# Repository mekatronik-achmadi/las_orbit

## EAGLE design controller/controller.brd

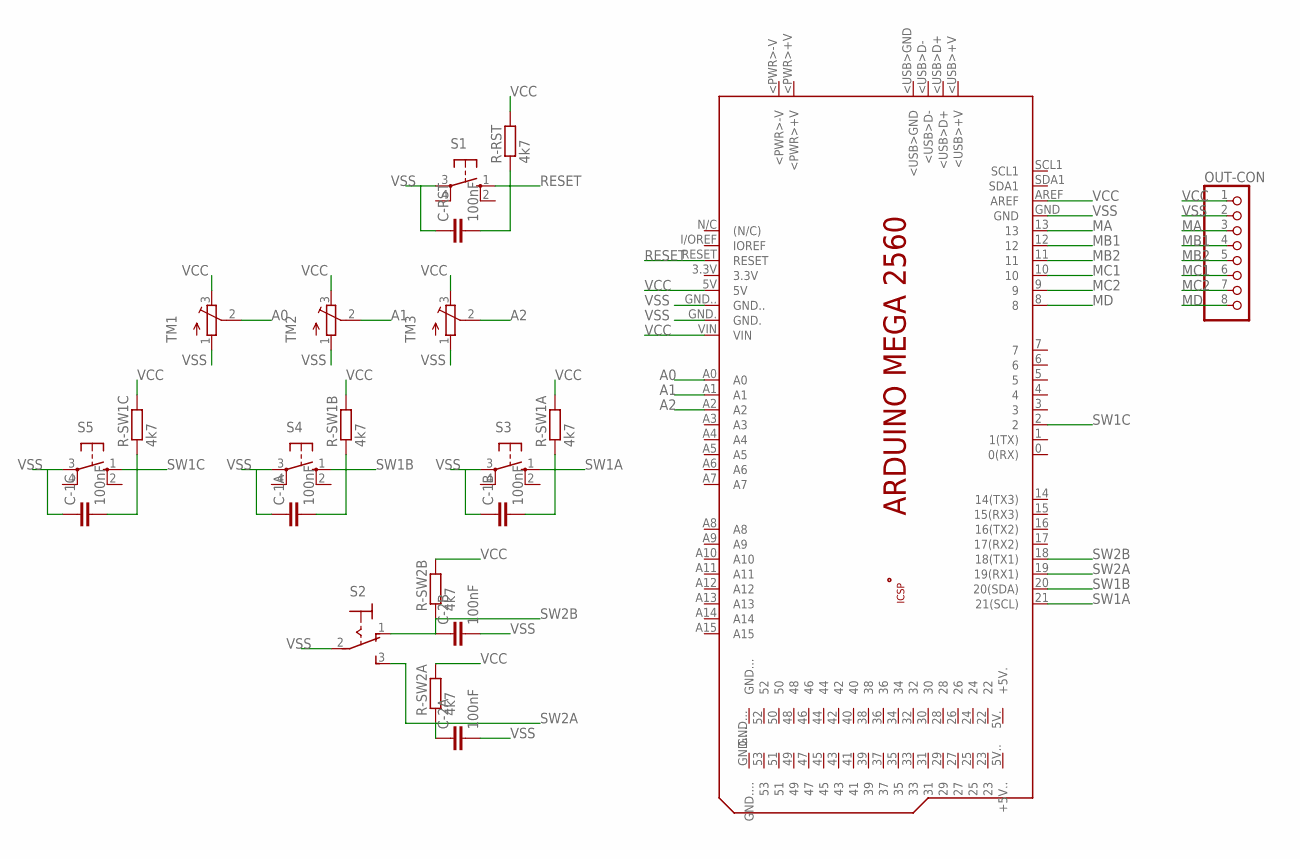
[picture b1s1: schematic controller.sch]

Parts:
C-1A, C-1B, C-1C, C-2A, C-2B: 100nF; C025-024X044
C-RST: 100nF; C025-024X044
OUT-CON: PINHD-1X8; 1X08
PCB1: ARDUINO_MEGA2560
R-RST: 4k7; 0204/7
R-SW1A, R-SW1B, R-SW1C, R-SW2A, R-SW2B: 4k7; 0204/7
S1, S3, S4, S5: 10-XX; B3F-10XX
S2: M9040P
TM1, TM2, TM3: TRIMPOT3386; TRIM-3386

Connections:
A0: PCB1.A0, TM1.2 (S)
A1: PCB1.A1, TM2.2 (S)
A2: PCB1.A2, TM3.2 (S)
MA: OUT-CON.3, PCB1.13
MB1: OUT-CON.4, PCB1.12
MB2: OUT-CON.5, PCB1.11
MC1: OUT-CON.6, PCB1.10
MC2: OUT-CON.7, PCB1.9
MD: OUT-CON.8, PCB1.8
RESET: C-RST.2, PCB1.RESET, R-RST.1, S1.1 (S)
SW1A: C-1B.2, PCB1.21 (21(SCL)), R-SW1A.1, S3.1 (S)
SW1B: C-1A.2, PCB1.20 (20(SDA)), R-SW1B.1, S4.1 (S)
SW1C: C-1C.2, PCB1.2, R-SW1C.1, S5.1 (S)
SW2A: C-2A.1, PCB1.19 (19(RX1)), R-SW2A.1, S2.3 (S)
SW2B: C-2B.1, PCB1.18 (18(TX1)), R-SW2B.1, S2.1 (O)
VCC: OUT-CON.1, PCB1.5V, PCB1.AREF, PCB1.VIN, R-RST.2, R-SW1A.2, R-SW1B.2, R-SW1C.2, R-SW2A.2, R-SW2B.2, TM1.3 (E), TM2.3 (E), TM3.3 (E)
VSS: C-1A.1, C-1B.1, C-1C.1, C-2A.2, C-2B.2, C-RST.1, OUT-CON.2, PCB1.GND, PCB1.GND., PCB1.GND.., S1.3, S2.2, S3.3, S4.3, S5.3, TM1.1 (A), TM2.1 (A), TM3.1 (A)

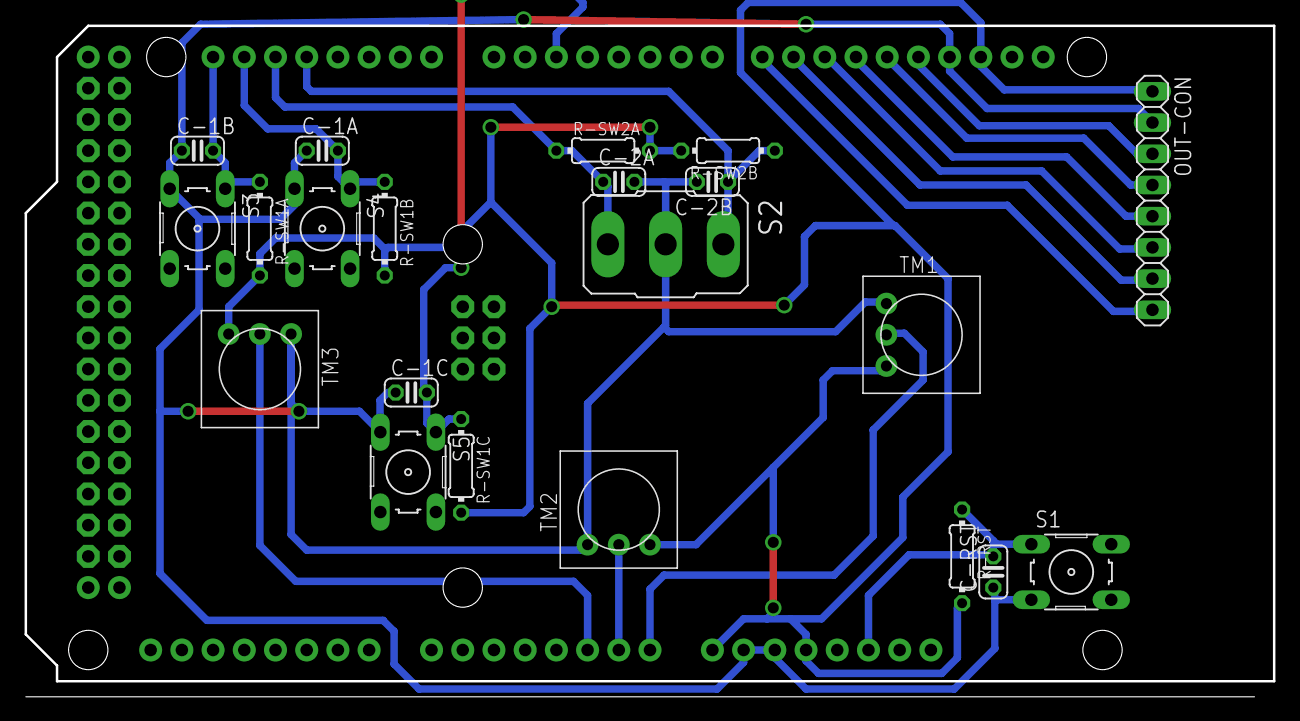
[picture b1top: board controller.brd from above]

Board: 2 copper layers, 101.6 x 54.6 mm, 22 parts (1 on the bottom side), 17 nets.

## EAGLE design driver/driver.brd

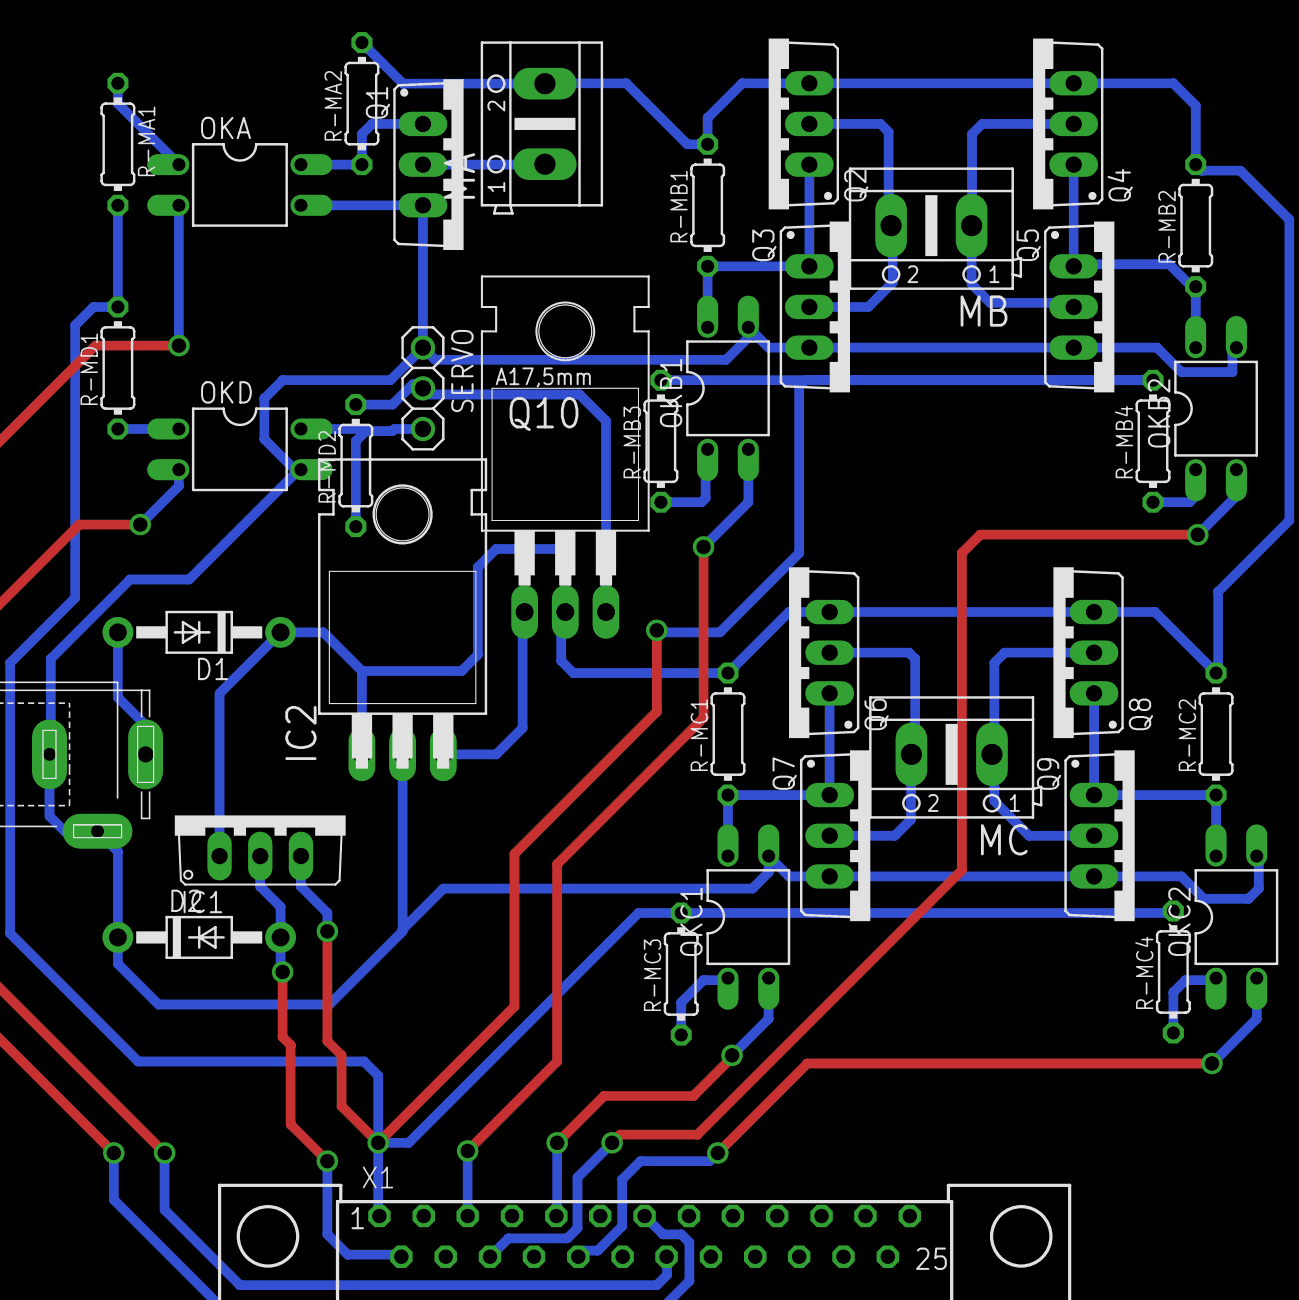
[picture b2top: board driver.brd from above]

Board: 2 copper layers, 38 parts (0 on the bottom side), 30 nets.

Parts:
D1, D2: 1N4004; DO41-10
IC1: 7805TV; TO220V
IC2: 7806T; TO220H
J1: SPC4077
MA: AK500/2
MB: AK500/2
MC: AK500/2
OKA: PC817; DIL04
OKB1, OKB2: PC817; DIL04
OKC1, OKC2: PC817; DIL04
OKD: PC817; DIL04
Q1, Q3, Q5, Q7, Q9: IRF530; TO220BV
Q2, Q4, Q6, Q8: IRF9530; TO220BV
Q10: TIP31C; TO220
R-MA1: 330; 0204/7
R-MA2: 4k7; 0204/7
R-MB1, R-MB2: 4k7; 0204/7
R-MB3, R-MB4: 330; 0204/7
R-MC1, R-MC2: 4k7; 0204/7
R-MC3, R-MC4: 330; 0204/7
R-MD1: 330; 0204/7
R-MD2: 4k7; 0204/7
SERVO: 1X03
X1: M25-HD-20

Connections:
6V: Q10.3, R-MD2.2, SERVO.2
24V: D1.C, IC1.1, IC2.1, MA.2, Q2.S, Q4.S, Q6.S, Q8.S, Q10.2, R-MA2.2, R-MB1.2, R-MB2.2, R-MC1.2, R-MC2.2
GND: D2.C, IC2.2, J1.1, J1.2, OKA.3, OKB1.3, OKB2.3, OKC1.3, OKC2.3, OKD.3, Q1.S, Q3.S, Q5.S, Q7.S, Q9.S, SERVO.1
MA: OKA.2, X1.7
MB1: OKB1.2, X1.3
MB2: OKB2.2, X1.16
MC1: OKC1.2, X1.5
MC2: OKC2.2, X1.18
MD: OKD.2, X1.20
MD-SERVO: OKD.4, R-MD2.1, SERVO.3
unnamed: OKA.4, Q1.G, R-MA2.1
unnamed: OKA.1, R-MA1.1
unnamed: MB.2, Q2.D, Q3.D
unnamed: MA.1, Q1.D
unnamed: MB.1, Q4.D, Q5.D
unnamed: OKB1.1, R-MB3.1
unnamed: OKB2.1, R-MB4.1
unnamed: MC.2, Q6.D, Q7.D
unnamed: OKB2.4, Q4.G, Q5.G, R-MB2.1
unnamed: OKB1.4, Q2.G, Q3.G, R-MB1.1
unnamed: MC.1, Q8.D, Q9.D
unnamed: OKC2.4, Q8.G, Q9.G, R-MC2.1
unnamed: OKC1.4, Q6.G, Q7.G, R-MC1.1
unnamed: OKC1.1, R-MC3.1
unnamed: OKC2.1, R-MC4.1
unnamed: OKD.1, R-MD1.1
unnamed: D1.A, J1.3
unnamed: IC2.3, Q10.1
VCC: IC1.3, R-MA1.2, R-MB3.2, R-MB4.2, R-MC3.2, R-MC4.2, R-MD1.2, X1.1
VSS: D2.A, IC1.2, X1.14

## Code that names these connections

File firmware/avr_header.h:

#ifndef AVR_HEADER
#define AVR_HEADER

#include <avr/io.h>
#include <avr/interrupt.h>
#include <util/delay.h>
#include <inttypes.h>
#include <stdio.h>
#include <stdlib.h>
#include <avr/eeprom.h>
#include <avr/pgmspace.h>

#include "las_uart.h"
#include "las_adc.h"
#include "las_tim.h"

#define LED 7 //B
#define MB1 6 //B
#define MB2 5 //B
#define MA  4 //H

#define SW2A 2 //D
#define SW2B 3 //D
#define SW1C 4 //E

#define TRFILLER 0
#define TRRAILLING 1
#define TRSERVO 2

#define IRQ_Start sei()

#endif

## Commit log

2015-06-05 Circuit manufacturing
2015-06-05 Add egde-line on top layer
2015-06-23 test with timer
2016-05-22 sudah selesai
